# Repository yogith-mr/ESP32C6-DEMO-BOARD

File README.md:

# 🚀 ESP32-C6 Development Board

## 📌 Overview
This project showcases the complete design and development of a custom **ESP32-C6 Development Board**, including schematic capture and PCB layout using KiCad. The board is designed for embedded systems and IoT applications, focusing on reliable hardware design, signal integrity, and efficient routing.

---

## 🎯 Objectives
- Design a custom ESP32-C6 based hardware platform  
- Implement robust power distribution and signal routing  
- Develop a compact and optimized PCB layout  
- Prepare the design for fabrication and real-world deployment  

---

## 🛠️ Design Details

### 🔹 Schematic Design
- Designed using **KiCad**
- Includes ESP32-C6 module, power supply circuitry, and essential interfaces  
- Proper decoupling capacitors and component selection applied  

### 🔹 PCB Layout
- Multi-layer PCB design  
- Optimized component placement for performance and compactness  
- Ground planes and power routing carefully implemented  

### 🔹 Routing
- Clean and structured trace routing  
- Signal integrity considerations applied  
- EMI-aware design practices followed  

## 📂 Project Structure

- `schematic/` → KiCad schematic files  
- `pcb/` → PCB layout files  
- `bom/` → Bill of Materials  
- `images/` → Design screenshots  
- `docs/` → Additional documentation (optional)

---

## 📸 Design Preview

### 🔹 Schematic

### 🔹 PCB Layout

### 🔹 3D View

---

## 📊 Bill of Materials
- Available in the `/bom` directory  
- Contains all components used in the design  

---

## ⚙️ Tools & Technologies
- **KiCad** (Schematic & PCB Design)  
- **ESP32-C6 Module**  
- PCB Design Principles & Layout Techniques  

---

## 🚀 Applications
- IoT Devices  
- Embedded Systems Development  
- Wireless Communication Projects  
- Prototyping and Hardware Testing  

---

## 👤 Author
**Yogith M R**  
VLSI Engineer | Digital Design | Embedded Systems | PCB Design  

📧 mryogith@gmail.com  
🔗 LinkedIn: https://www.linkedin.com/in/yogith-gowda-07b594296  

---

## ⭐ Notes
This project demonstrates practical skills in **hardware design, PCB layout, and embedded systems development**, aligned with real-world engineering workflows.

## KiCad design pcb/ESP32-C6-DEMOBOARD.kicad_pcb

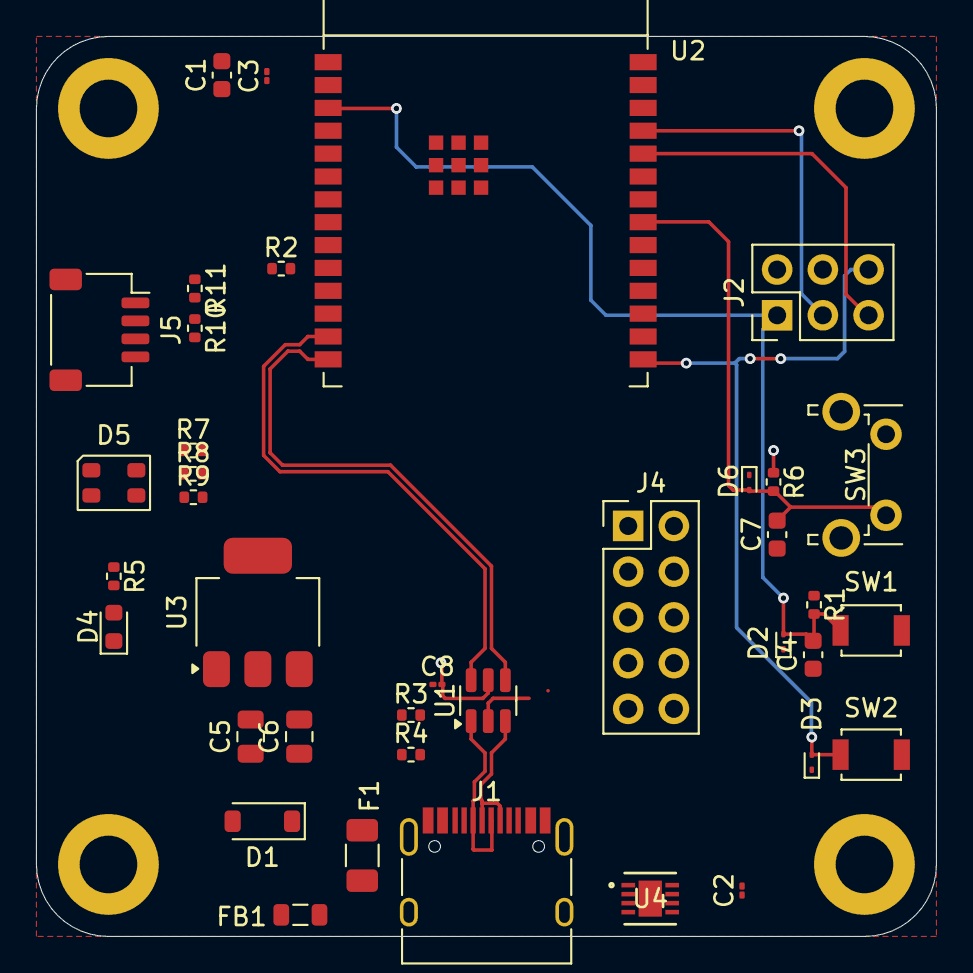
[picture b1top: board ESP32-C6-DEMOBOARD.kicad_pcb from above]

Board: 4 copper layers, 50.0 x 50.0 mm, 42 parts (0 on the bottom side), 33 nets.

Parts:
C1, C4, C7: 10u; C_0603_1608Metric
C2, C3, C8: 100n; C_01005_0402Metric
C5, C6: 22u; C_0805_2012Metric
D1: 1N5817; D_SOD-123
D2, D3, D6: ESD9B3.3; D_SOD-923
D4: GREEN; LED_0603_1608Metric
D5: CLV1L-FKB; LED_Cree-PLCC4_3.2x2.8mm_CCW
F1: Polyfuse; Fuse_1206_3216Metric
FB1: BLM21PG220; L_0805_2012Metric
H1, H2, H3, H4: MountingHole; MountingHole_3.2mm_M3_DIN965_Pad
J1: USB_C_Receptacle_USB2.0_16P; USB_C_Receptacle_HRO_TYPE-C-31-M-12
J2: Pin 2X3; PinHeader_2x03_P2.54mm_Vertical
J4: Pin 2x5; PinHeader_2x05_P2.54mm_Vertical
J5: Conn_01x04; JST_SH_SM04B-SRSS-TB_1x04-1MP_P1.00mm_Horizontal
R1, R2, R6: 10k; R_0402_1005Metric
R3, R4: 5.1k; R_0402_1005Metric
R5, R7, R8, R9: 1k; R_0402_1005Metric
R10, R11: 2.2k; R_0402_1005Metric
SW1, SW2: SW_SPST; SW_SPST_B3U-1000P
SW3: SW_SPST; SW_Tactile_SPST_Angled_PTS645Vx31-2LFS
U1: USBLC6-2SC6; SOT-23-6
U2: ESP32-C6-WROOM-1
U3: LM1117MP-3.3; SOT-223-3_TabPin2
U4: HDC3022; WSON8_DEJ_TEX

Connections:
+3.3V: C1.1, C2.1, C3.1, C5.2, C8.1, D5.1 (A), J2.2, J4.1, J4.2, J5.2, R1.1, R2.1, R5.1, R6.1, R10.1, R11.1, U1.5 (VBUS), U2.2 (3V3), U3.2 (VO), U4.5 (VDD), U4.6 (~RESET)
+5V: C6.2, D1.1 (K), U3.3 (VI)
/BOOT9: D3.2 (A2), J2.6, SW2.2 (B), U2.15 (GPIO9)
/B_LED: R7.2, U2.5 (MTDI/GPIO5/ADC1_CH5)
/CC1: J1.A5 (CC1), R3.1
/CC2: J1.B5 (CC2), R4.1
/CS: J4.4, U2.16 (GPIO18)
/D+: J1.A6 (D+), J1.B6 (D+), U1.3 (I/O2)
/D-: J1.A7 (D-), J1.B7 (D-), U1.1 (I/O1)
/ESP_EN: C4.2, D2.2 (A2), J2.1, R1.2, SW1.2 (B), U2.3 (EN/CHIP_PU)
/ESP_RXT: J2.5, U2.24 (U0RXD/GPIO17)
/ESP_TXT: J2.3, U2.25 (U0TXD/GPIO16)
/G_LED: R8.2, U2.4 (MTMS/GPIO4/ADC1_CH4)
/IRQ: J4.8, U2.12 (GPIO11)
/MISO: J4.7, U2.18 (GPIO20)
/MOSI: J4.5, U2.19 (GPIO21)
/R_LED: R9.2, U2.26 (GPIO3/ADC1_CH3)
/SCL: U2.7 (MTDO/GPIO7), U4.4 (SCL)
/SDL: U2.6 (MTCK/GPIO6/ADC1_CH6), U4.1 (SDA)
/USB_D+: U1.4 (I/O2), U2.14 (GPIO13/USB_D+)
/USB_D-: U1.6 (I/O1), U2.13 (GPIO12/USB_D-)
/USER_SW: C7.2, D6.2 (A2), R6.2, SW3.2 (B), U2.21 (GPIO23)
GND: C1.2, C2.2, C3.2, C4.1, C5.1, C6.1, C7.1, C8.2, D2.1 (A1), D3.1 (A1), D4.1 (K), D6.1 (A1), J1.A1 (GND), J1.A12 (GND), J1.B1 (GND), J1.B12 (GND), J1.S1 (SHIELD), J2.4, J4.9, J4.10, J5.1, R3.2, R4.2, SW1.1 (A), SW2.1 (A), SW3.1 (A), U1.2 (GND), U2.1 (GND), U2.28 (GND), U2.29 (GND), U3.1 (GND), U4.2 (ADDR), U4.7 (ADDR1), U4.8 (GND)
unnamed: D1.2 (A), FB1.2
unnamed: D4.2 (A), R5.2
unnamed: D5.4 (BK), R7.1
unnamed: D5.3 (GK), R8.1
unnamed: D5.2 (RK), R9.1
unnamed: F1.1, J1.A4 (VBUS), J1.A9 (VBUS), J1.B4 (VBUS), J1.B9 (VBUS)
unnamed: F1.2, FB1.1
unnamed: J5.3, R11.2
unnamed: J5.4, R10.2
unnamed: R2.2, U2.10 (GPIO8)
